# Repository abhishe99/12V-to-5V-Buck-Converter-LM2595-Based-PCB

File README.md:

# -12V-to-5V-Buck-Converter-LM2595-Based-PCB-Design-in-KiCad-
Complete 12V to 5V Buck Converter design using KiCad. Includes schematic, PCB layout, DRC clean-up, and Gerber file generation.
# 12V to 5V Buck Converter – PCB Design (KiCad)

This project showcases the schematic and PCB layout of a 12V to 5V Buck Converter based on the LM2595S-5.0 regulator IC. Designed using **KiCad 9.0**, the board is EMI-conscious, DRC-clean, and Gerber-ready.

---

## 🔧 Technical Specifications

- **Input:** 12V DC  
- **Output:** 5V DC (regulated)  
- **Controller IC:** LM2595S-5.0  
- **Key Components:**
  - C1 & C3: 220µF Electrolytic Capacitors  
  - C2 & C4: 0.1µF Ceramic Capacitors  
  - Inductor: 68µH Shielded  
  - Diode: SS34 Schottky  
  - Ferrite Bead: 6000Ω @ 100 MHz (input side)

---

## 📁 Files Included

- `buck_converter.sch` – Schematic file  
- `buck_converter.kicad_pcb` – PCB layout  
- `3D_view.png` – 3D rendered image  
- `gerber/` – Gerber output folder  
- `README.md` – Documentation  

---

## 🚀 Highlights

- Full DRC clearance  
- Copper pour and proper grounding  
- EV domain-ready board  
- Clean layout for low EMI/RFI risk  

---

## 📌 Tools Used

- KiCad 9.0 (schematic, PCB, 3D viewer)

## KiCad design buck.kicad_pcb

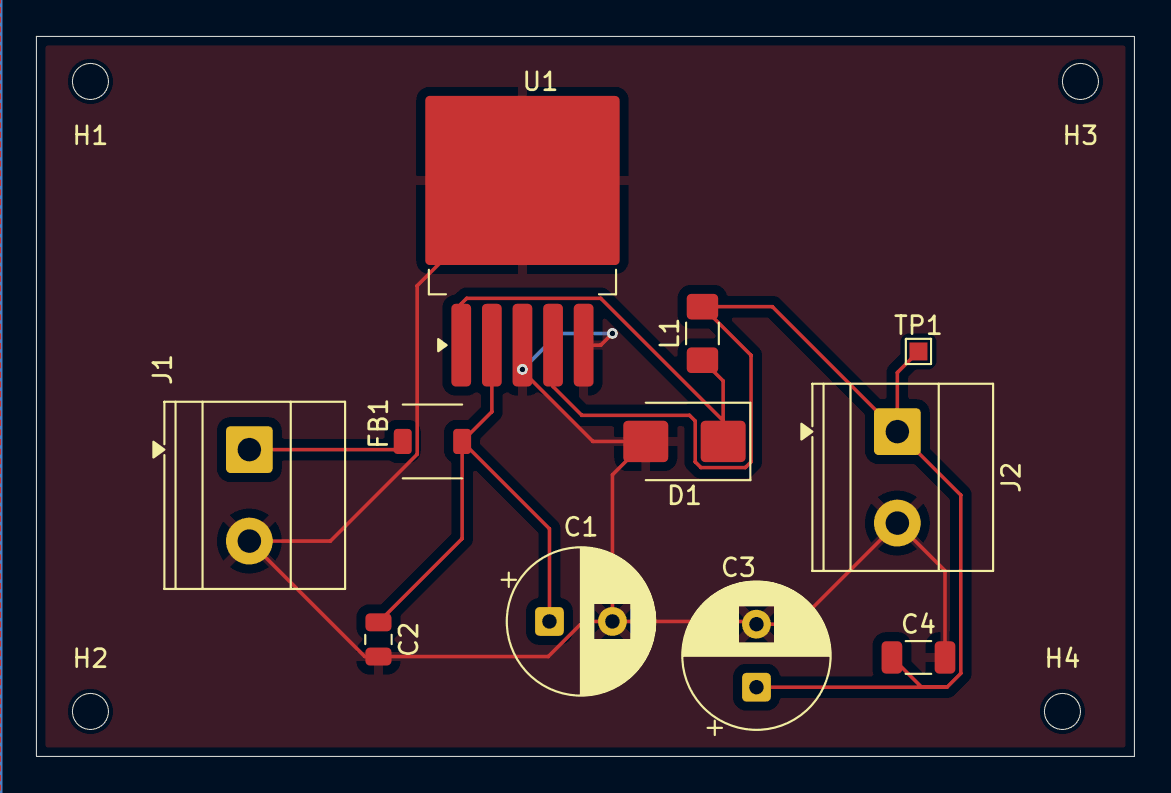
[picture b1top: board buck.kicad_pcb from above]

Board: 2 copper layers, 61.0 x 40.0 mm, 15 parts (0 on the bottom side), 5 nets.

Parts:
C1, C3: 220uF; CP_Radial_D8.0mm_P3.50mm
C2: 0.1uF; C_0805_2012Metric
C4: 0.1uF; C_1206_3216Metric
D1: SS34; D_SMB
FB1: 6000 ohm@100MHz; L_Murata_DEM35xxC
H1, H2, H3, H4: MountingHole; MountingHole_2mm
J1, J2: Screw_Terminal_01x02; TerminalBlock_Phoenix_MKDS-1,5-2-5.08_1x02_P5.08mm_Horizont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
L1: 68uH; L_1206_3216Metric_Pad1.42x1.75mm_HandSolder
TP1: TestPoint; TestPoint_Pad_1.0x1.0mm
U1: LM2595S-5; TO-263-5_TabPin3

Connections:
GND: C1.2, C2.2, C3.2, C4.2, D1.2 (A), J1.2, J2.2, U1.3 (GND), U1.5 (ON/~OFF)
unnamed: D1.1 (K), L1.1, U1.1 (OUT)
unnamed: C1.1, C2.1, FB1.2, U1.2 (VIN)
Vin: FB1.1, J1.1
Vout: C3.1, C4.1, J2.1, L1.2, TP1.1, U1.4 (FB)
